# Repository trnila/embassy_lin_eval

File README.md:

# LIN evaluation board for embassy
LIN eval board utilizing the Rust Embassy framework, featuring:
- 4x LEDs
- 1x RGB LED
- 1x Photoresistor for light sensing
- 1x One-Wire DS18B20 temperature sensor
- 3x jumpers to set board ID (0-7)

## Build and run

Connect debugger and run:

```shell-session
$ cargo run
```

To initiate LIN communication, connect the PEAK PLIN-USB interface and run the following command:
```shell-session
$ uv run ./commander.py
```

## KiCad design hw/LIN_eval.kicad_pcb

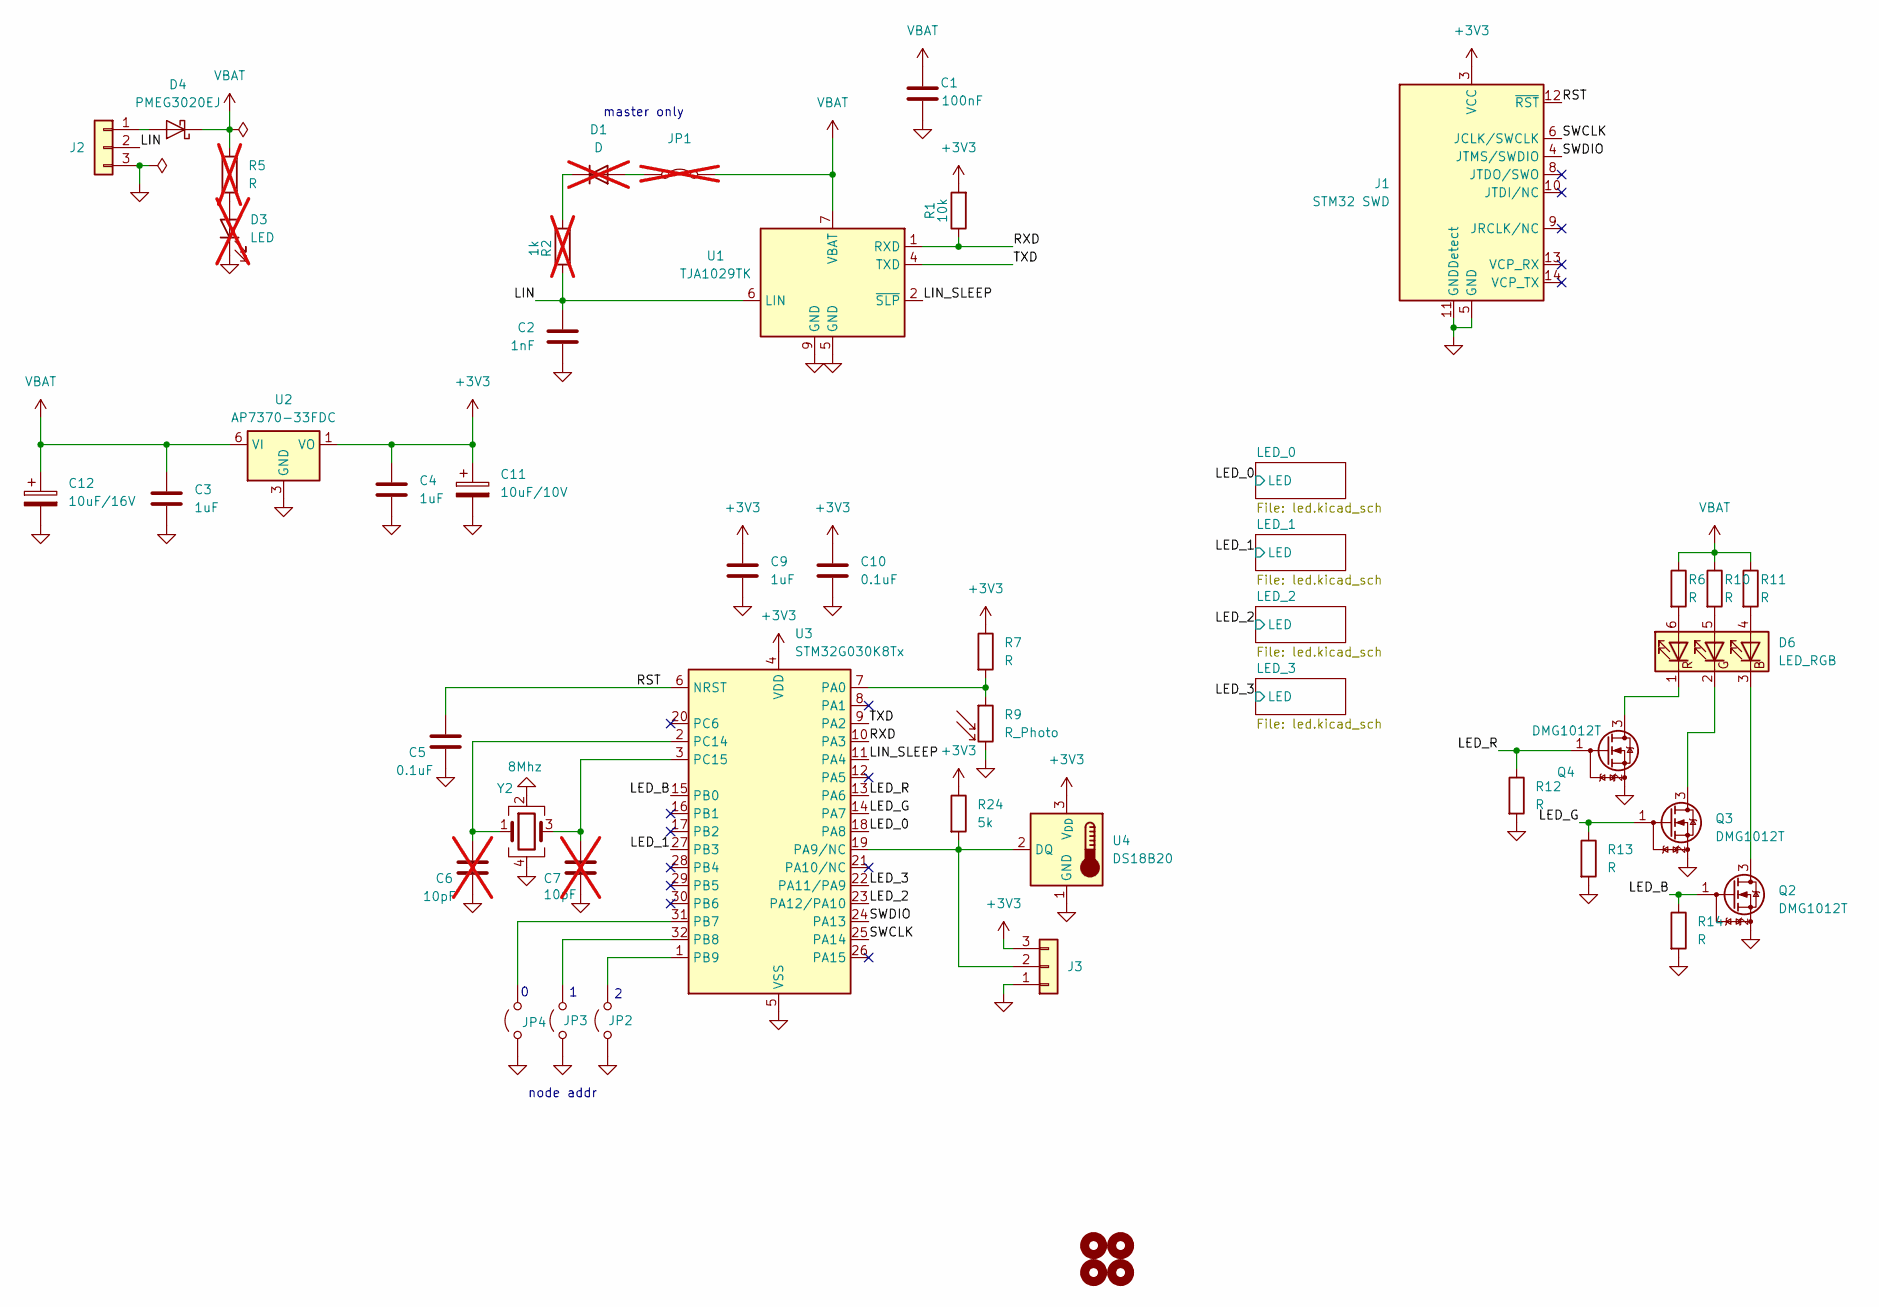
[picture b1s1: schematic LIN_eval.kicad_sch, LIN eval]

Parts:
C1: 100nF; C_0805_2012Metric_Pad1.18x1.45mm_HandSolder
C2: 1nF; C_0805_2012Metric_Pad1.18x1.45mm_HandSolder
C3, C4, C9: 1uF; C_0805_2012Metric_Pad1.18x1.45mm_HandSolder
C5, C10: 0.1uF; C_0805_2012Metric_Pad1.18x1.45mm_HandSolder
C6, C7: 10pF; C_0805_2012Metric_Pad1.18x1.45mm_HandSolder; not fitted
C11: 10uF/10V; CP_EIA-2012-12_Kemet-R_Pad1.30x1.05mm_HandSolder
C12: 10uF/16V; CP_EIA-3528-15_AVX-H_Pad1.50x2.35mm_HandSolder
D1: D; D_SOD-323_HandSoldering; not fitted
D3: LED; LED_0805_2012Metric_Pad1.15x1.40mm_HandSolder; not fitted
D4: PMEG3020EJ; D_SOD-323F
D6: LED_RGB; LED_RGB_5050-6
H1, H2, H3, H4: MountingHole; MountingHole_2.2mm_M2
J1: STM32 SWD; PinHeader_2x07_P1.27mm_Vertical_SMD
J2: Conn_01x03; PinHeader_1x03_P2.54mm_Vertical
J3: Conn_01x03; PinHeader_1x03_P1.27mm_Vertical
JP1: Jumper_2_Bridged; TestPoint_2Pads_Pitch2.54mm_Drill0.8mm; not fitted
JP2, JP3, JP4: Jumper_2_Open; TestPoint_2Pads_Pitch2.54mm_Drill0.8mm
Q2, Q3, Q4: DMG1012T; SOT-523
R1: 10k; R_0805_2012Metric_Pad1.20x1.40mm_HandSolder
R2: 1k; R_0805_2012Metric_Pad1.20x1.40mm_HandSolder; not fitted
R5: R; R_0805_2012Metric_Pad1.20x1.40mm_HandSolder; not fitted
R6, R7, R10, R11, R12, R13, R14: R; R_0805_2012Metric_Pad1.20x1.40mm_HandSolder
R9: R_Photo; R_LDR_5.0x4.1mm_P3mm_Vertical
R24: 5k; R_0805_2012Metric_Pad1.20x1.40mm_HandSolder
U1: TJA1029TK; DFN-8-1EP_3x3mm_P0.65mm_EP1.55x2.4mm
U2: AP7370-33FDC; DFN-6-1EP_2x2mm_P0.65mm_EP1.01x1.7mm
U3: STM32G030K8Tx; LQFP-32_7x7mm_P0.8mm
U4: DS18B20; TO-92_Inline
Y2: 8Mhz; Crystal_SMD_SeikoEpson_FA128-4Pin_2.0x1.6mm

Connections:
+3V3: C4.1, C9.1, C10.1, C11.1, J1.3 (VCC), J3.3, R1.2, R7.1, R24.1, U2.1 (VO), U3.4 (VDD), U4.3 (V_{DD})
/LED_0: U3.18 (PA8); also elsewhere on the board
/LED_1: U3.27 (PB3); also elsewhere on the board
/LED_2: U3.23 (PA12/PA10); also elsewhere on the board
/LED_3: U3.22 (PA11/PA9); also elsewhere on the board
/LED_B: Q2.1 (G), R14.1, U3.15 (PB0)
/LED_G: Q3.1 (G), R13.1, U3.14 (PA7)
/LED_R: Q4.1 (G), R12.1, U3.13 (PA6)
/LIN: C2.1, J2.2, R2.2, U1.6 (LIN)
/LIN_SLEEP: U1.2 (~SLP), U3.11 (PA4)
/RST: C5.1, J1.12 (~RST), U3.6 (NRST)
/RXD: R1.1, U1.1 (RXD), U3.10 (PA3)
/SWCLK: J1.6 (JCLK/SWCLK), U3.25 (PA14)
/SWDIO: J1.4 (JTMS/SWDIO), U3.24 (PA13)
/TXD: U1.4 (TXD), U3.9 (PA2)
GND: C1.2, C2.2, C3.2, C4.2, C5.2, C6.2, C7.2, C9.2, C10.2, C11.2, C12.2, D3.1 (K), J1.5 (GND), J1.7 (GND), J1.11 (GNDDetect), J2.3, J3.1, JP2.1 (A), JP3.1 (A), JP4.1 (A), Q2.2 (S), Q3.2 (S), Q4.2 (S), R9.2, R12.2, R13.2, R14.2, U1.5 (GND), U1.9 (GND), U2.3 (GND), U2.7 (GND), U3.5 (VSS), U4.1 (GND), Y2.2, Y2.4; also elsewhere on the board
unnamed: D1.2 (A), JP1.2 (B)
unnamed: D1.1 (K), R2.1
unnamed: D3.2 (A), R5.2
unnamed: D4.2 (A), J2.1
unnamed: D6.4 (BA), R11.2
unnamed: D6.3 (BK), Q2.3 (D)
unnamed: D6.5 (GA), R10.2
unnamed: D6.2 (GK), Q3.3 (D)
unnamed: D6.6 (RA), R6.2
unnamed: D6.1 (RK), Q4.3 (D)
unnamed: J3.2, R24.2, U3.19 (PA9/NC), U4.2 (DQ)
unnamed: JP2.2 (B), U3.1 (PB9)
unnamed: JP3.2 (B), U3.32 (PB8)
unnamed: JP4.2 (B), U3.31 (PB7)
unnamed: R7.2, R9.1, U3.7 (PA0)
unnamed: C6.1, U3.2 (PC14), Y2.1
unnamed: C7.1, U3.3 (PC15), Y2.3
VBAT: C1.1, C3.1, C12.1, D4.1 (K), JP1.1 (A), R5.1, R6.1, R10.1, R11.1, U1.7 (VBAT), U2.6 (VI); also elsewhere on the board

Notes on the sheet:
master only
node addr

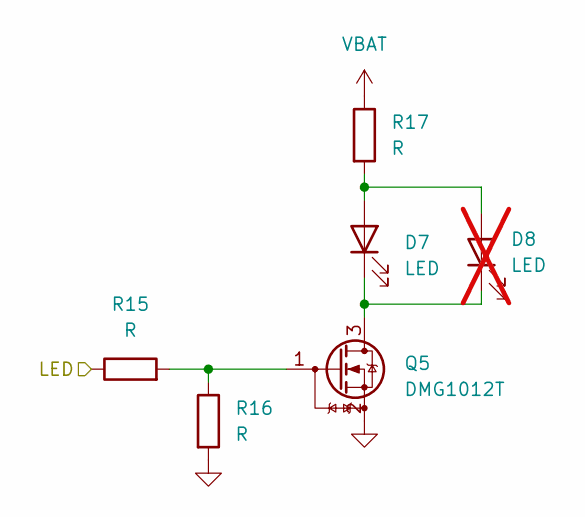
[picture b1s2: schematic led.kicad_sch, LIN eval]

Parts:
D7: LED; LED_D5.0mm
D8: LED; LED_0805_2012Metric_Pad1.15x1.40mm_HandSolder; not fitted
Q5: DMG1012T; SOT-523
R15, R16, R17: R; R_0805_2012Metric_Pad1.20x1.40mm_HandSolder

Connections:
/LED_1: R15.1; also elsewhere on the board
GND: Q5.2 (S), R16.2; also elsewhere on the board
unnamed: D7.2 (A), D8.2 (A), R17.2
unnamed: D7.1 (K), D8.1 (K), Q5.3 (D)
unnamed: Q5.1 (G), R15.2, R16.1
VBAT: R17.1; also elsewhere on the board

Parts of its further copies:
D2, D9, D11: LED; LED_D5.0mm
D5, D10, D12: LED; LED_0805_2012Metric_Pad1.15x1.40mm_HandSolder; not fitted
Q1, Q6, Q7: DMG1012T; SOT-523
R3, R4, R8, R18, R19, R20, R21, R22, R23: R; R_0805_2012Metric_Pad1.20x1.40mm_HandSolder

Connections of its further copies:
/LED_0: R3.1; also elsewhere on the board
/LED_2: R18.1; also elsewhere on the board
/LED_3: R21.1; also elsewhere on the board
GND: Q1.2 (S), Q6.2 (S), Q7.2 (S), R4.2, R19.2, R22.2; also elsewhere on the board
unnamed: D2.2 (A), D5.2 (A), R8.2
unnamed: D2.1 (K), D5.1 (K), Q1.3 (D)
unnamed: D9.2 (A), D10.2 (A), R20.2
unnamed: D9.1 (K), D10.1 (K), Q6.3 (D)
unnamed: D11.2 (A), D12.2 (A), R23.2
unnamed: D11.1 (K), D12.1 (K), Q7.3 (D)
unnamed: Q1.1 (G), R3.2, R4.1
unnamed: Q6.1 (G), R18.2, R19.1
unnamed: Q7.1 (G), R21.2, R22.1
VBAT: R8.1, R20.1, R23.1; also elsewhere on the board

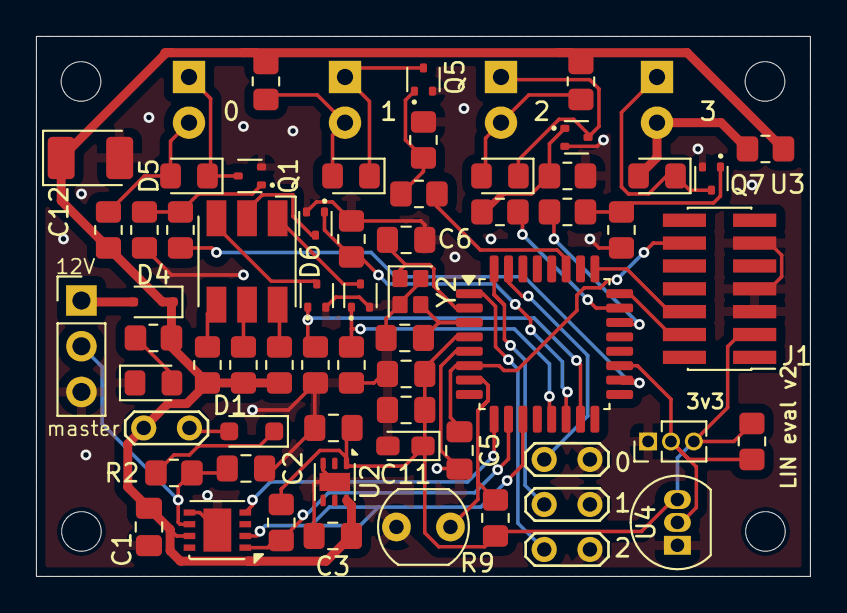
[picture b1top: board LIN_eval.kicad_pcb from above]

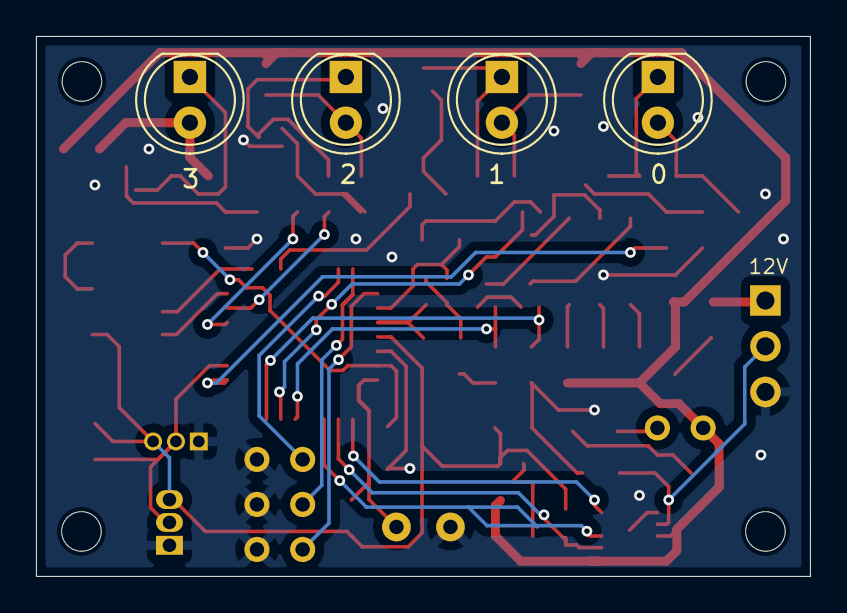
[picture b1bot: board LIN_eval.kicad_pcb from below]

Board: 2 copper layers, 43.0 x 30.0 mm, 70 parts (4 on the bottom side), 46 nets.

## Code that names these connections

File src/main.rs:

#![no_std]
#![no_main]

mod ds18b20;
mod lin_slave_driver;
mod lin_slave_handler;
mod onewire;
mod rgb;
mod signals;

use cortex_m::singleton;
use defmt::{error, info};
use lin_slave_handler::LinHandler;
use onewire::OneWire;
#[cfg(not(feature = "defmt"))]
use panic_halt as _;
use signals::{SIGNAL_LEDS, SIGNAL_PHOTORESISTOR, SIGNAL_RGB, SIGNAL_TEMPERATURE};
#[cfg(feature = "defmt")]
use {defmt_rtt as _, panic_probe as _};

use crate::rgb::RGBLed;
use embassy_executor::Spawner;
use embassy_stm32::{
    adc::AdcChannel,
    gpio::OutputType,
    mode::Async,
    time::khz,
    timer::simple_pwm::{PwmPin, SimplePwm},
    usart::{RingBufferedUartRx, Uart, UartTx},
    wdg::IndependentWatchdog,
};
use embassy_stm32::{adc::AnyAdcChannel, timer::Channel as TimChannel};
use embassy_stm32::{
    adc::{Adc, SampleTime},
    peripherals::*,
};
use embassy_stm32::{
    bind_interrupts,
    gpio::{Input, Level, Output, Pull, Speed},
    usart::{self, BufferedUart},
};
use embassy_time::{Duration, Timer};
use lin_slave_driver::lin_slave_driver;

bind_interrupts!(struct UARTIRqs {
    USART2 => usart::BufferedInterruptHandler<USART2>;
});

bind_interrupts!(struct OneWireUsartIrqs {
    USART1 => usart::InterruptHandler<USART1>;
});

#[embassy_executor::task]
async fn rgb_task(mut led: RGBLed<TIM3>) {
    loop {
        let req = SIGNAL_RGB.wait().await;
        led.set(req.r, req.g, req.b);
    }
}

#[embassy_executor::task]
async fn leds_task(mut leds: [Output<'static>; 4]) {
    loop {
        let req = SIGNAL_LEDS.wait().await;
        for (led, state) in leds.iter_mut().zip(req) {
            led.set_level(match state {
                0 => Level::Low,
                _ => Level::High,
            });
        }
    }
}

#[embassy_executor::task]
async fn lin_slave_task(uart: BufferedUart<'static>, _lin_sleep: Output<'static>, board_id: u8) {
    let handler = LinHandler::new(board_id);
    lin_slave_driver(uart, handler).await;
}

#[embassy_executor::task]
async fn adc_task(
    mut adc: Adc<'static, ADC1>,
    mut dma: DMA1_CH1,
    mut channel: AnyAdcChannel<ADC1>,
) {
    let read_buffer: &mut [u16; 2] = singleton!(ADC_BUF: [u16; 2] = [0; 2]).unwrap();
    let mut vrefint_channel = adc.enable_vrefint().degrade_adc();

    loop {
        adc.read(
            &mut dma,
            [
                (&mut vrefint_channel, SampleTime::CYCLES160_5),
                (&mut channel, SampleTime::CYCLES160_5),
            ]
            .into_iter(),
            read_buffer,
        )
        .await;

        let vrefint = read_buffer[1];
        let measured = read_buffer[0];

        const VREFINT_MV: u32 = 1212; // mV
        let measured_mv: u16 = (u32::from(measured) * VREFINT_MV / u32::from(vrefint)) as u16;

        SIGNAL_PHOTORESISTOR.signal(measured_mv);

        info!("vrefint: {} PA0: {} {}mV", vrefint, measured, measured_mv);
        Timer::after(Duration::from_millis(500)).await;
    }
}

#[embassy_executor::task]
async fn watchdog_task(mut wdg: IndependentWatchdog<'static, IWDG>) {
    loop {
        Timer::after_secs(1).await;
        wdg.pet();
    }
}

fn get_board_id(pins: &[Input]) -> u8 {
    pins.iter()
        .enumerate()
        .map(|(pos, pin)| {
            if pin.is_low() {
                2u8.pow((pins.len() - 1 - pos) as u32)
            } else {
                0
            }
        })
        .sum()
}

#[embassy_executor::main]
async fn main(spawner: Spawner) {
    let p = embassy_stm32::init(Default::default());
    let mut wdg = IndependentWatchdog::new(p.IWDG, 2_000_000);
    wdg.unleash();
    spawner.spawn(watchdog_task(wdg)).unwrap();

    SIGNAL_TEMPERATURE.signal(None);

    let board_id = get_board_id(&[
        Input::new(p.PB9, Pull::Up),
        Input::new(p.PB8, Pull::Up),
        Input::new(p.PB7, Pull::Up),
    ]);
    info!("Board id: {}", board_id);

    let leds = [
        Output::new(p.PA8, Level::Low, Speed::Low),
        Output::new(p.PB3, Level::Low, Speed::Low),
        Output::new(p.PA12, Level::Low, Speed::Low),
        Output::new(p.PA11, Level::Low, Speed::Low),
    ];
    let lin_sleep = Output::new(p.PA4, Level::High, Speed::Low);

    let rgb_blue_ch = PwmPin::new_ch1(p.PA6, OutputType::PushPull);
    let rgb_red_ch = PwmPin::new_ch2(p.PA7, OutputType::PushPull);
    let rgb_green_ch = PwmPin::new_ch3(p.PB0, OutputType::PushPull);

    let pwm = SimplePwm::new(
        p.TIM3,
        Some(rgb_blue_ch),
        Some(rgb_red_ch),
        Some(rgb_green_ch),
        None,
        khz(1),
        Default::default(),
    );
    let pwm_rgb = RGBLed::new(pwm, TimChannel::Ch2, TimChannel::Ch3, TimChannel::Ch1);

    let config = {
        let mut config = usart::Config::default();
        config.baudrate = 19200;
        //config.extended_feature = Some(ExtendedFeature::LIN);
        config
    };

    let tx_buf: &mut [u8; 32] = singleton!(TX_BUF: [u8; 32] = [0; 32]).unwrap();
    let rx_buf: &mut [u8; 32] = singleton!(RX_BUF: [u8; 32] = [0; 32]).unwrap();
    let uart = BufferedUart::new(p.USART2, UARTIRqs, p.PA3, p.PA2, tx_buf, rx_buf, config).unwrap();

    let adc = Adc::new(p.ADC1);
    let dma = p.DMA1_CH1;
    let pa0 = p.PA0.degrade_adc();

    let onewire_usart = Uart::new_half_duplex(
        p.USART1,
        p.PA9,
        OneWireUsartIrqs,
        p.DMA1_CH2,
        p.DMA1_CH3,
        usart::Config::default(),
        // Enable readback so we can read sensor pulling data low while transmission is in progress
        usart::HalfDuplexReadback::Readback,
        usart::HalfDuplexConfig::OpenDrainExternal,
    )
    .unwrap();

    const BUFFER_SIZE: usize = 16;
    let (tx, rx) = onewire_usart.split();
    let rx_buf: &mut [u8; BUFFER_SIZE] =
        singleton!(TX_BUF: [u8; BUFFER_SIZE] = [0; BUFFER_SIZE]).unwrap();
    let rx = rx.into_ring_buffered(rx_buf);
    let onewire = OneWire::new(tx, rx);

    spawner
        .spawn(lin_slave_task(uart, lin_sleep, board_id))
        .unwrap();
    spawner.spawn(rgb_task(pwm_rgb)).unwrap();
    spawner.spawn(leds_task(leds)).unwrap();
    spawner.spawn(adc_task(adc, dma, pa0)).unwrap();
    spawner.spawn(ds18b20_task(onewire)).unwrap();
}

#[embassy_executor::task]
async fn ds18b20_task(onewire: OneWire<UartTx<'static, Async>, RingBufferedUartRx<'static>>) {
    let mut sensor: ds18b20::Ds18b20<UartTx<'_, Async>, RingBufferedUartRx<'_>> =
        ds18b20::Ds18b20::new(onewire);
    loop {
        SIGNAL_TEMPERATURE.signal(match sensor.raw_temperature().await {
            Ok(raw_temperature) => {
                info!("Temperature: {}°C", raw_temperature as f32 / 16.);
                Some(raw_temperature)
            }
            Err(_) => {
                error!("Failed to read temperature");
                None
            }
        });

        Timer::after(Duration::from_secs(1)).await;
    }
}

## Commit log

2024-10-22 created rust project
2024-10-22 dont print location
2024-10-22 Added pre-commit
2024-10-22 Toggle all LEDs
2024-10-22 Added lin
2024-10-22 bring up adc
2024-10-22 removed fmt.rs
2024-10-22 Added ci
2024-10-22 Use tim1 as an embassy time source
2024-10-22 Use pwm for RGB led
2024-10-22 Changing RGB via LIN
2024-10-22 Snake led animation via LIN
2024-10-22 Split LIN and signals to own files
2024-10-22 Measure photoresistor mV and respond to master LIN frames
2024-10-22 Calculate board id from pins
2024-10-22 removed main loop, lin_sleep moved to lin task so its not deconfigured
2024-10-22 Dont set RGB at startup
2024-10-22 poetry: disable packaging
2024-10-22 Added README.md
2024-11-14 lin_slave: use frame_id instead of PID in processing functions
2024-11-14 Split LIN to driver and frame handler
2024-11-14 lin_slave_handler: offset LIN frames by board_id * 5
2024-11-15 commander.py: communicate with multiple boards
2024-11-15 Added watchdog with 1 second trigger and 2 second dead-time
2024-11-15 using unreleased patch for detecting wrong PIDs in lin-bus-rs
2024-11-15 commander: frame merges signals instead of overwritting whole frame
2024-11-18 commander.py: added shell for testing
2024-12-20 hw: added pdf schematics
2024-12-20 upgraded to latest embassy
2024-12-22 hw: version v2 with improvements
    - removed LIN UART RX/TX from debugger connector as it drives signal from two sources
    - added 5k pull-up to DS18B20 1-Wire bus
    - added 1.27mm connector for additional devices on 1-Wire bus
    - shifted address jumpers little bit farther from debugger connector
2025-01-01 Measure temperature with DS18B20 on onewire bus
2025-09-02 migrate from poetry to uv
2025-09-02 commander: install gnureadline dep
2025-09-02 pre-commit: upgrade hooks
2025-09-02 ci: install clippy component
